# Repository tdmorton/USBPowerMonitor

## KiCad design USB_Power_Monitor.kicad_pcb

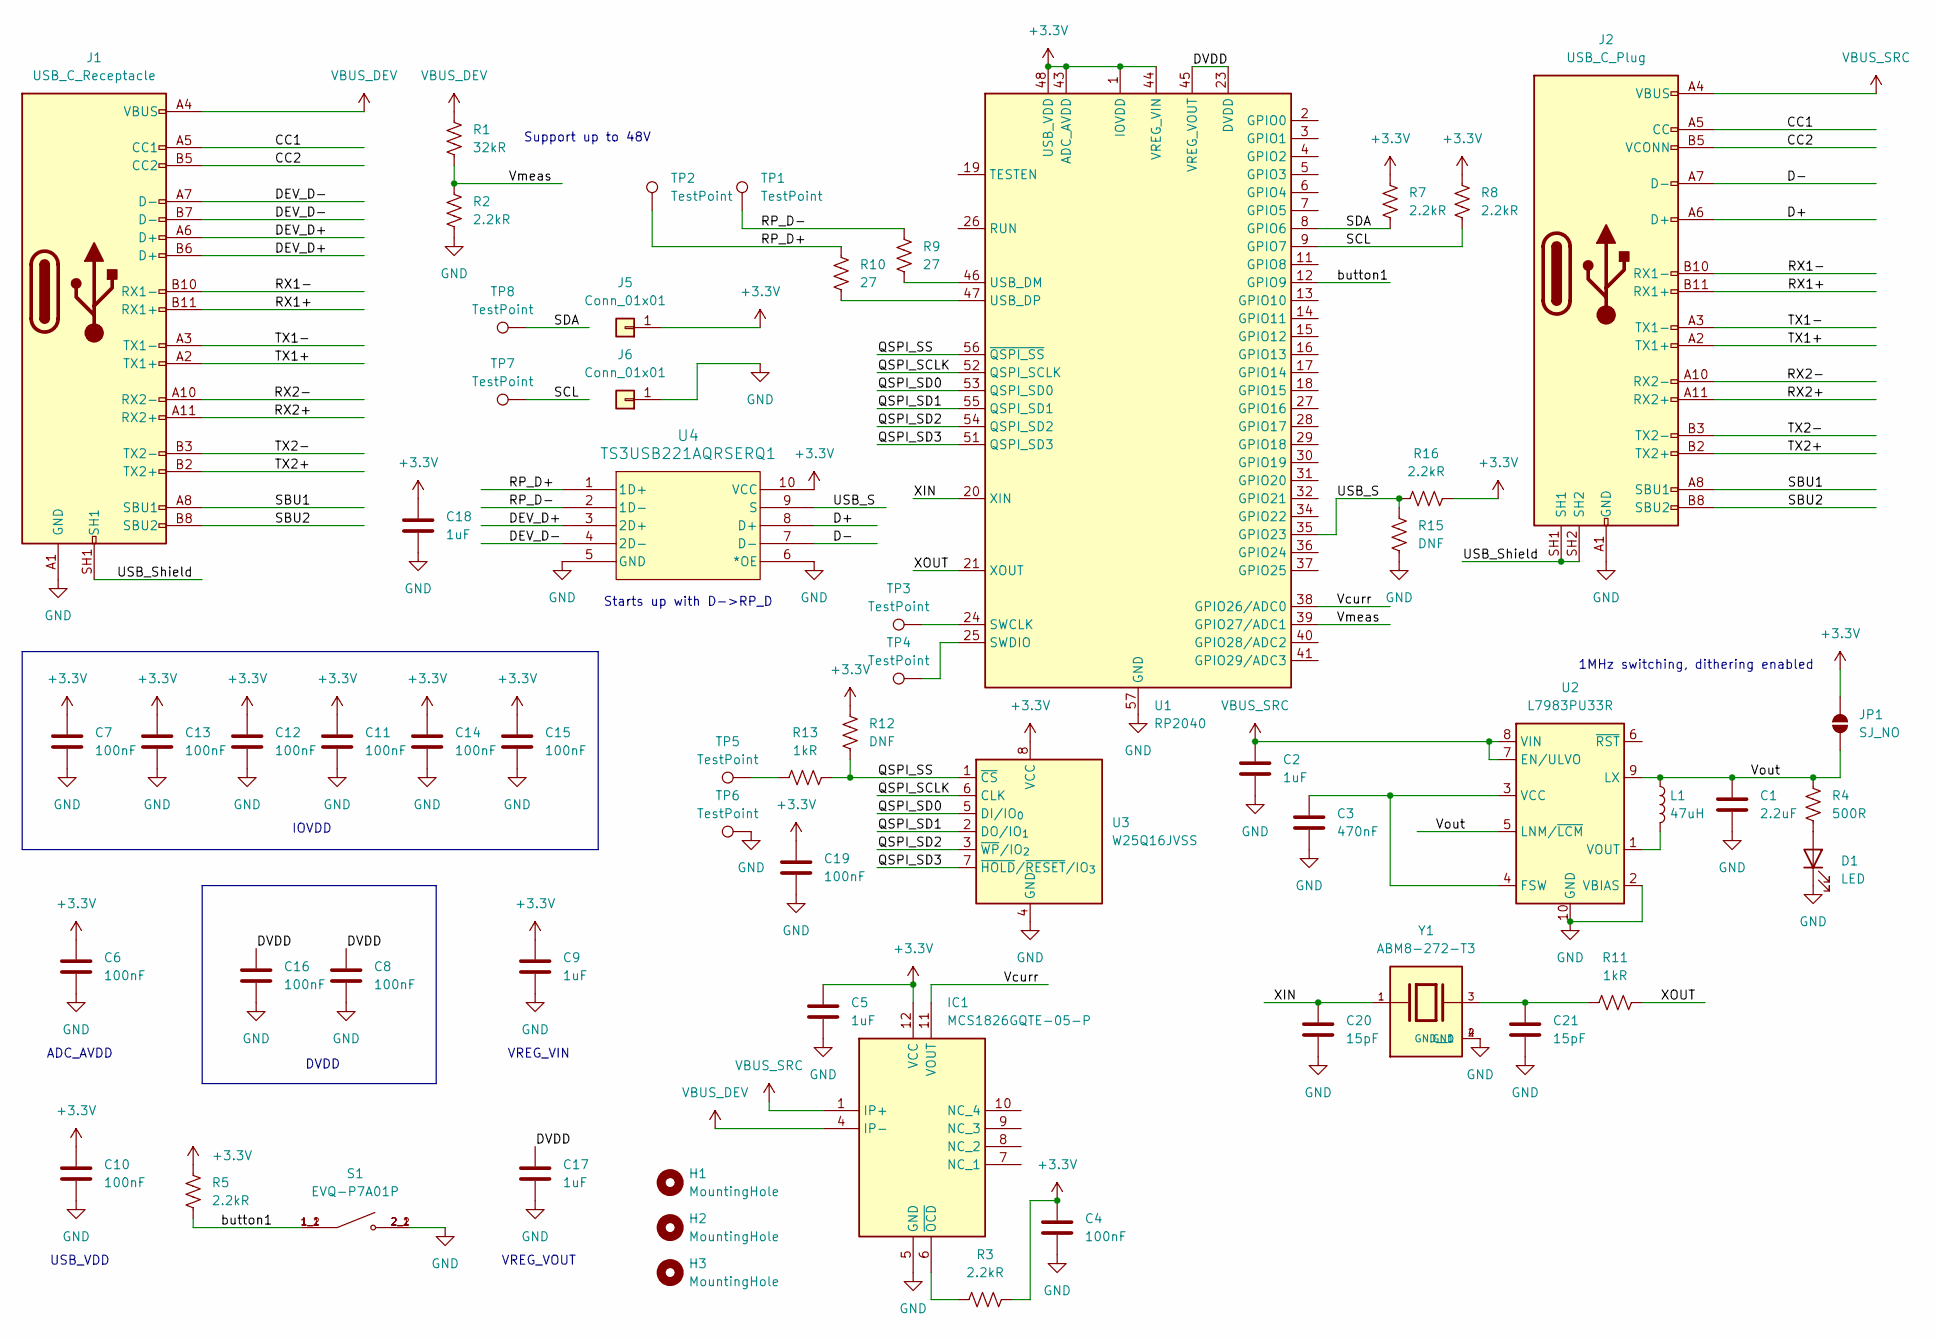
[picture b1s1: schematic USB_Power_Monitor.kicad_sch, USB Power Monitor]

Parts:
C1: 2.2uF; C_0603_1608Metric; Manufacturer_Part_Number KGM15BR50J225KT; Mouser Part Number 581-KGM15BR50J225KT
C2: 1uF; C_0603_1608Metric; Manufacturer_Part_Number C1608X7R2A105K080AC; Mouser Part Number 810-C1608X7R2A105K08
C3: 470nF; C_0603_1608Metric; Manufacturer_Part_Number GRM188R71E474KA12J; Mouser Part Number 81-GRM188R71E474KA2J
C4, C6, C7, C8, C10, C11, C12, C13, C14, C15, C16, C19: 100nF; C_0603_1608Metric; Manufacturer_Part_Number CC0603ZRY5V8BB104; Mouser Part Number 603-C0603ZRY5V8BB104
C5, C9, C17, C18: 1uF; C_0603_1608Metric; Manufacturer_Part_Number CC0603KRX5R8BB105; Mouser Part Number 603-CC603KRX5R8BB105
C20, C21: 15pF; C_0603_1608Metric; Manufacturer_Part_Number CC0603JRNPO9BN150
D1: LED; C_0603_1608Metric; Manufacturer_Part_Number TLMS1100-GS15; Mouser Part Number 78-TLMS1100-GS15
H1, H2, H3: MountingHole; MountingHole_2.2mm_M2
IC1: MCS1826GQTE-05-P; MCS1826GQTE05P; Mouser Part Number 946-MCS1826GQTE-05-P
J1: USB_C_Receptacle; CONN24_4056-03-A_GCT; Manufacturer_Part_Number USB4056-03-A; Mouser Part Number 640-USB4056-03-A
J2: USB_C_Plug; MOLEX_1054440011; Manufacturer_Part_Number 1054440011; Mouser Part Number 538-105444-0011
J5, J6: Conn_01x01; PinHeader_1x01_P2.54mm_Vertical
JP1: SJ_NO; SolderJumper-2_P1.3mm_Open_RoundedPad1.0x1.5mm
L1: 47uH; L_0805_2012Metric; Manufacturer_Part_Number MLZ2012M470WT000; Mouser Part Number 810-MLZ2012M470WT000
R1: 32kR; C_0603_1608Metric; Manufacturer_Part_Number RC0603FR-0732K4L
R2, R3, R5, R7, R8, R16: 2.2kR; C_0603_1608Metric; Manufacturer_Part_Number RC0603FR-072K2L
R4: 500R; C_0603_1608Metric; Manufacturer_Part_Number RC0603FR-07499RL
R9, R10: 27; C_0603_1608Metric; Manufacturer_Part_Number RC0603FR-0727RL
R11, R13: 1kR; C_0603_1608Metric; Manufacturer_Part_Number RC0603FR-071KL
R12, R15: DNF; C_0603_1608Metric
S1: EVQ-P7A01P; SW_EVQ-P7A01P; PARTREV 2022.4
TP1, TP2, TP3, TP4, TP5, TP6, TP7, TP8: TestPoint; TestPoint_Pad_1.0x1.0mm
U1: RP2040; QFN-56-1EP_7x7mm_P0.4mm_EP3.2x3.2mm; Manufacturer_Part_Number RP2040
U2: L7983PU33R; ST_DFN-10-1EP_3x3mm_P0.5mm_EP0.62x0.98mm; Manufacturer_Part_Number L7983PU33R; Mouser Part Number 511-L7983PU33R
U3: W25Q16JVSS; SOIC-8_5.3x5.3mm_P1.27mm; Manufacturer_Part_Number W25Q16JVSSIQ TR
U4: TS3USB221AQRSERQ1; RSE10; Manufacturer_Part_Number TS3USB221AQRSERQ1
Y1: ABM8-272-T3; XTAL_ABM8-272-T3; PARTREV 07-29-20

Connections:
+3.3V: C4.1, C5.1, C6.1, C7.1, C9.1, C10.1, C11.1, C12.1, C13.1, C14.1, C15.1, C18.1, C19.1, IC1.12 (VCC), J5.1, JP1.2 (B), R3.1, R5.1, R7.1, R8.1, R12.2, R16.2, U1.1 (IOVDD), U1.10 (IOVDD), U1.22 (IOVDD), U1.33 (IOVDD), U1.42 (IOVDD), U1.43 (ADC_AVDD), U1.44 (VREG_VIN), U1.48 (USB_VDD), U1.49 (IOVDD), U3.8 (VCC), U4.10 (VCC)
/CC1: J1.A5 (CC1), J2.A5 (CC)
/CC2: J1.B5 (CC2), J2.B5 (VCONN)
/D+: J2.A6 (D+), U4.8 (D+)
/D-: J2.A7 (D-), U4.7 (D-)
/DEV_D+: J1.A6 (D+), J1.B6 (D+), U4.3 (2D+)
/DEV_D-: J1.A7 (D-), J1.B7 (D-), U4.4 (2D-)
/DVDD: C8.1, C16.1, C17.1, U1.23 (DVDD), U1.45 (VREG_VOUT), U1.50 (DVDD)
/QSPI_SCLK: U1.52 (QSPI_SCLK), U3.6 (CLK)
/QSPI_SD0: U1.53 (QSPI_SD0), U3.5 (DI/IO_{0})
/QSPI_SD1: U1.55 (QSPI_SD1), U3.2 (DO/IO_{1})
/QSPI_SD2: U1.54 (QSPI_SD2), U3.3 (~WP/IO_{2})
/QSPI_SD3: U1.51 (QSPI_SD3), U3.7 (~HOLD/~RESET/IO_{3})
/QSPI_SS: R12.1, R13.2, U1.56 (~QSPI_SS), U3.1 (~CS)
/RP_D+: R10.2, TP2.1, U4.1 (1D+)
/RP_D-: R9.2, TP1.1, U4.2 (1D-)
/RX1+: J1.B11 (RX1+), J2.B11 (RX1+)
/RX1-: J1.B10 (RX1-), J2.B10 (RX1-)
/RX2+: J1.A11 (RX2+), J2.A11 (RX2+)
/RX2-: J1.A10 (RX2-), J2.A10 (RX2-)
/SBU1: J1.A8 (SBU1), J2.A8 (SBU1)
/SBU2: J1.B8 (SBU2), J2.B8 (SBU2)
/SCL: R8.2, TP7.1, U1.9 (GPIO7)
/SDA: R7.2, TP8.1, U1.8 (GPIO6)
/TX1+: J1.A2 (TX1+), J2.A2 (TX1+)
/TX1-: J1.A3 (TX1-), J2.A3 (TX1-)
/TX2+: J1.B2 (TX2+), J2.B2 (TX2+)
/TX2-: J1.B3 (TX2-), J2.B3 (TX2-)
/USB_S: R15.2, R16.1, U1.35 (GPIO23), U4.9 (S)
/USB_Shield: J1.SH1, J1.SH2, J1.SH3, J1.SH4, J2.SH1, J2.SH2
/Vcurr: IC1.11 (VOUT), U1.38 (GPIO26/ADC0)
/Vmeas: R1.2, R2.1, U1.39 (GPIO27/ADC1)
/Vout: C1.1, JP1.1 (A), L1.1, R4.1, U2.5 (LNM/~LCM), U2.9 (LX)
/XIN: C20.1, U1.20 (XIN), Y1.1
/XOUT: R11.2, U1.21 (XOUT)
/button1: R5.2, S1.1_1, S1.1_2, U1.12 (GPIO9)
GND: C1.2, C2.2, C3.2, C4.2, C5.2, C6.2, C7.2, C8.2, C9.2, C10.2, C11.2, C12.2, C13.2, C14.2, C15.2, C16.2, C17.2, C18.2, C19.2, C20.2, C21.2, D1.1 (K), IC1.5 (GND), J1.A1 (GND), J1.A12 (GND), J1.B1 (GND), J1.B12 (GND), J2.A1 (GND), J2.A12 (GND), J2.B1 (GND), J2.B12 (GND), J6.1, R2.2, R15.1, S1.2_1, S1.2_2, TP6.1, U1.57 (GND), U2.2 (VBIAS), U2.10 (GND), U2.11 (GND), U3.4 (GND), U4.5 (GND), U4.6 (*OE), Y1.2 (GND), Y1.4 (GND__1)
unnamed: C21.1, R11.1, Y1.3
unnamed: D1.2 (A), R4.2
unnamed: IC1.6 (~OCD), R3.2
unnamed: R13.1, TP5.1
unnamed: TP3.1, U1.24 (SWCLK)
unnamed: TP4.1, U1.25 (SWDIO)
unnamed: R9.1, U1.46 (USB_DM)
unnamed: R10.1, U1.47 (USB_DP)
unnamed: C3.1, U2.3 (VCC), U2.4 (FSW)
unnamed: L1.2, U2.1 (VOUT)
VBUS_DEV: IC1.4 (IP-), J1.A4 (VBUS), J1.A9 (VBUS), J1.B4 (VBUS), J1.B9 (VBUS), R1.1
VBUS_SRC: C2.1, IC1.1 (IP+), J2.A4 (VBUS), J2.A9 (VBUS), J2.B4 (VBUS), J2.B9 (VBUS), U2.7 (EN/ULVO), U2.8 (VIN)

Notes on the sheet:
USB_VDD
Starts up with D->RP_D
ADC_AVDD
1MHz switching, dithering enabled
VREG_VOUT
VREG_VIN
Support up to 48V
DVDD
IOVDD

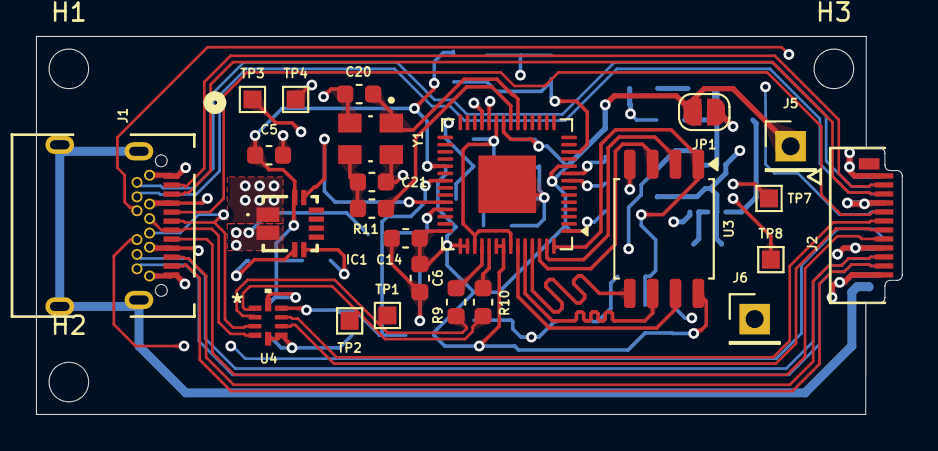
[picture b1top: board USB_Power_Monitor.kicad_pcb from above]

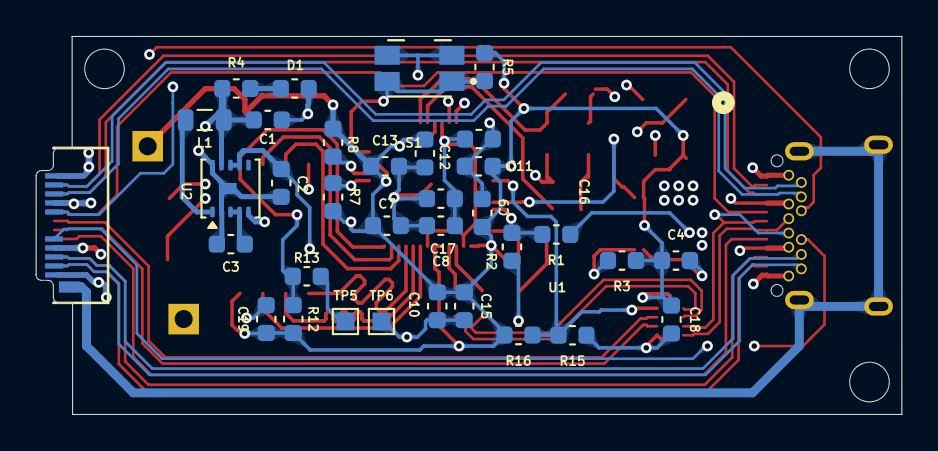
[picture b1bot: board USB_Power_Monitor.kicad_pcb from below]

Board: 4 copper layers, 48.1 x 21.0 mm, 60 parts (33 on the bottom side), 49 nets.

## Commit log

2026-02-23 Adding initial project
2026-02-26 finished routing RP2040
2026-03-01 finished routing most components, no power yet
2026-03-09 Main power zone defined
2026-03-21 All nets routed, need to clean up text and check errors
2026-03-21 Fixed overlapping silkscreen
2026-03-22 All DRC cleared except board outline and some weird footprint issues
2026-03-22 Add .gitignore, starting fab process
2026-03-22 Clean up ignored files
2026-03-22 Added SWD test points, roughly length matched qspi
2026-03-23 Increase 3.3V trace width, add teardrops, generate fab files
2026-03-24 Fix BOM part numbers
2026-03-26 Fixed GND plane, add mounting holes
